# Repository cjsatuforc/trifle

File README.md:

# Trifle Flight Control Unit

Trifle is a flight controller board for quadcopters. As the name implies, the board itself does very little except
breakout a microcontroller board and contain an intertial measurement unit.

## Active components
The main active components contained on the board are:
 - Teensy 3.1 (https://www.pjrc.com/teensy/teensy31.html) microcontroller board, based on the Freescale Kinetis K20 SoC family
 - Adafruit 10-DOF inertial measurement unit (http://www.adafruit.com/product/1604)

## Specification
The provided layout is such that the board can be hand-assembled on a perf-board. Ports include:
 - 1 power connector (5V)
 - 1 voltage measurement port (12.6V max, i.e. LiPo battery 3S)
 - 4 main PWM outputs, used to control motor speed
 - 2 auxiliary PWM outputs
 - 2 UARTs, for telemetry and GPS (telemetry is also used as radio control)
 - 1 ultrasonic distance sensor interface (using echo and trigger pins)

## Software
Currently work-in-progress, the goal is to provide support for the PX4 autopilot [firmware](https://github.com/jodersky/px4-firmware).

## License
Design files are licensed under a Creative Commons Attribution 4.0 International License.

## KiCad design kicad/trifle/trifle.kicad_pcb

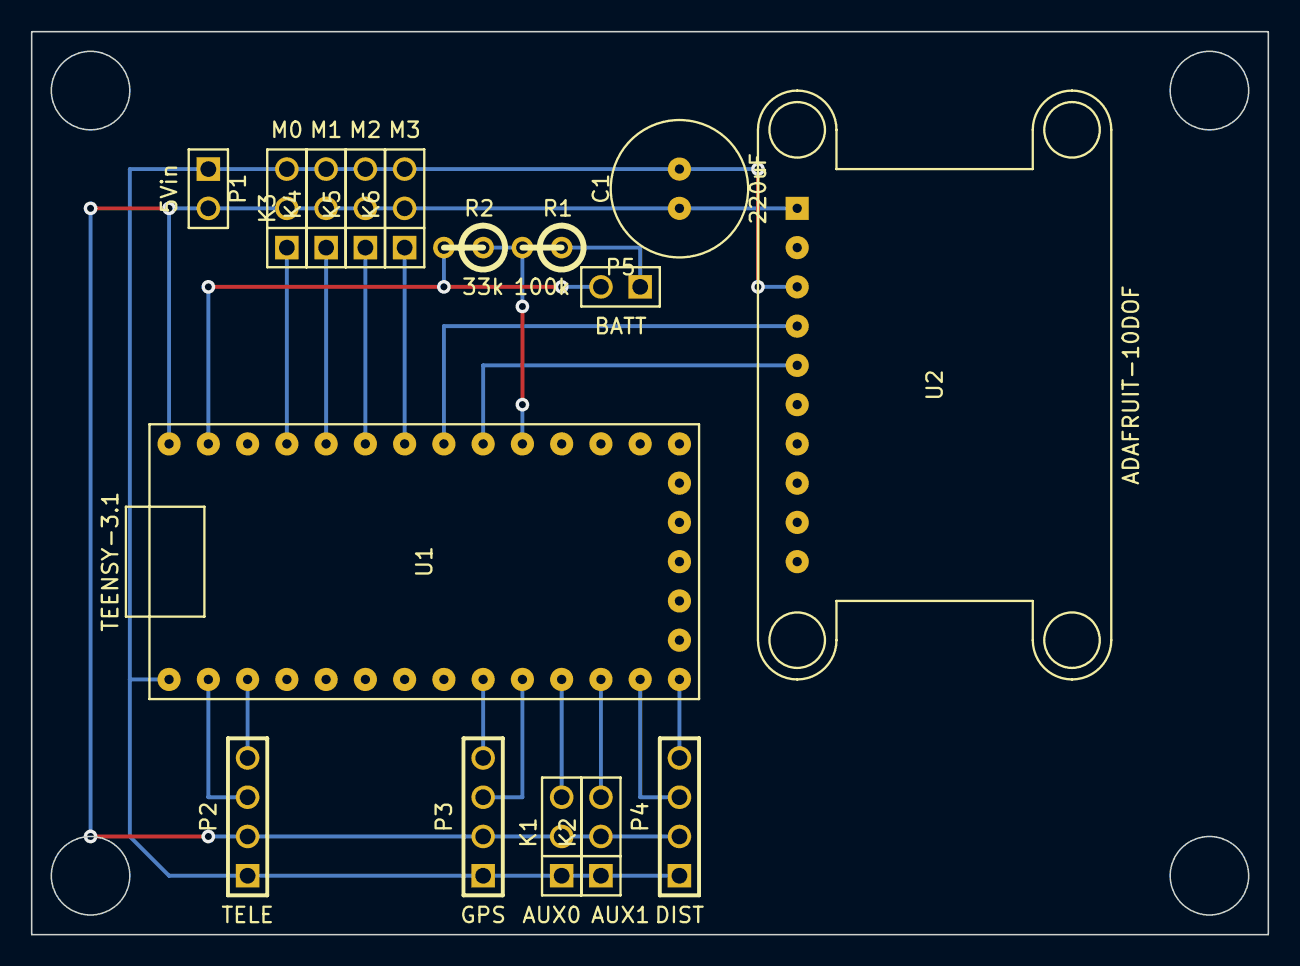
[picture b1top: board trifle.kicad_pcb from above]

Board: 2 copper layers, 80.0 x 58.4 mm, 16 parts (0 on the bottom side), 19 nets.

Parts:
C1: 220uF; CTOP
K1: AUX0; PIN_ARRAY_3X1
K2: AUX1; PIN_ARRAY_3X1
K3: M0; PIN_ARRAY_3X1
K4: M1; PIN_ARRAY_3X1
K5: M2; PIN_ARRAY_3X1
K6: M3; PIN_ARRAY_3X1
P1: 5Vin; PIN_ARRAY_2X1
P2: TELE; PIN_ARRAY_4x1
P3: GPS; PIN_ARRAY_4x1
P4: DIST; PIN_ARRAY_4x1
P5: BATT; PIN_ARRAY_2X1
R1: 100k; R1
R2: 33k; R1
U1: TEENSY-3.1; teensy-3.1
U2: ADAFRUIT-10DOF; adafruit-10dof

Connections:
/AGND: P5.2, R2.2, U1.32
GND: C1.2, K1.1, K2.1, K3.3, K4.3, K5.3, K6.3, P1.1, P2.1, P3.1, P4.1, U1.1, U2.3
unnamed: K1.3, U1.11
unnamed: P4.4, U1.14
unnamed: P4.3, U1.13
unnamed: K2.3, U1.12
unnamed: P3.4, U1.9
unnamed: P3.3, U1.10
unnamed: P2.3, U1.2
unnamed: P2.4, U1.3
unnamed: U1.25, U2.5
unnamed: U1.26, U2.4
unnamed: K4.1, U1.29
unnamed: K5.1, U1.28
unnamed: K6.1, U1.27
unnamed: R1.2, R2.1, U1.24
unnamed: K3.1, U1.30
unnamed: P5.1, R1.1
VCC: C1.1, K1.2, K2.2, K3.2, K4.2, K5.2, K6.2, P1.2, P2.2, P3.2, P4.2, U1.33, U2.1

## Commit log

2015-02-28 add datasheets of active components used
